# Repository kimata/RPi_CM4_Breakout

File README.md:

# RPi_CM4_Breakout

## 概要

Raspberry Pi Compute Module 4 から，通常の Raspberry Pi にあるピンヘッダを取り出す基板です．
サイズと穴位置は秋月のユニバーサル基板Ｃタイプに合わせてあります．

おまけで，I2C 用のピンヘッダ用のランドも設けています．

## 外観

## 回路図

## 基板の発注について

Raspberry Pi Compute Module 4 との接続に使う 100 ピンコネクタは手はんだが難しいので，この部分だけ基板メーカで実装してもらうのがおすすめです．

Elecrow にオーダーする際のシートを misc/Elecrow-PCBA-Quotation.xlsx においておきましたので参考にしてください．このファイルとガーバーデータを送れば製造できます．

料金は，私が製造したときは，送料込みで $168 でした．

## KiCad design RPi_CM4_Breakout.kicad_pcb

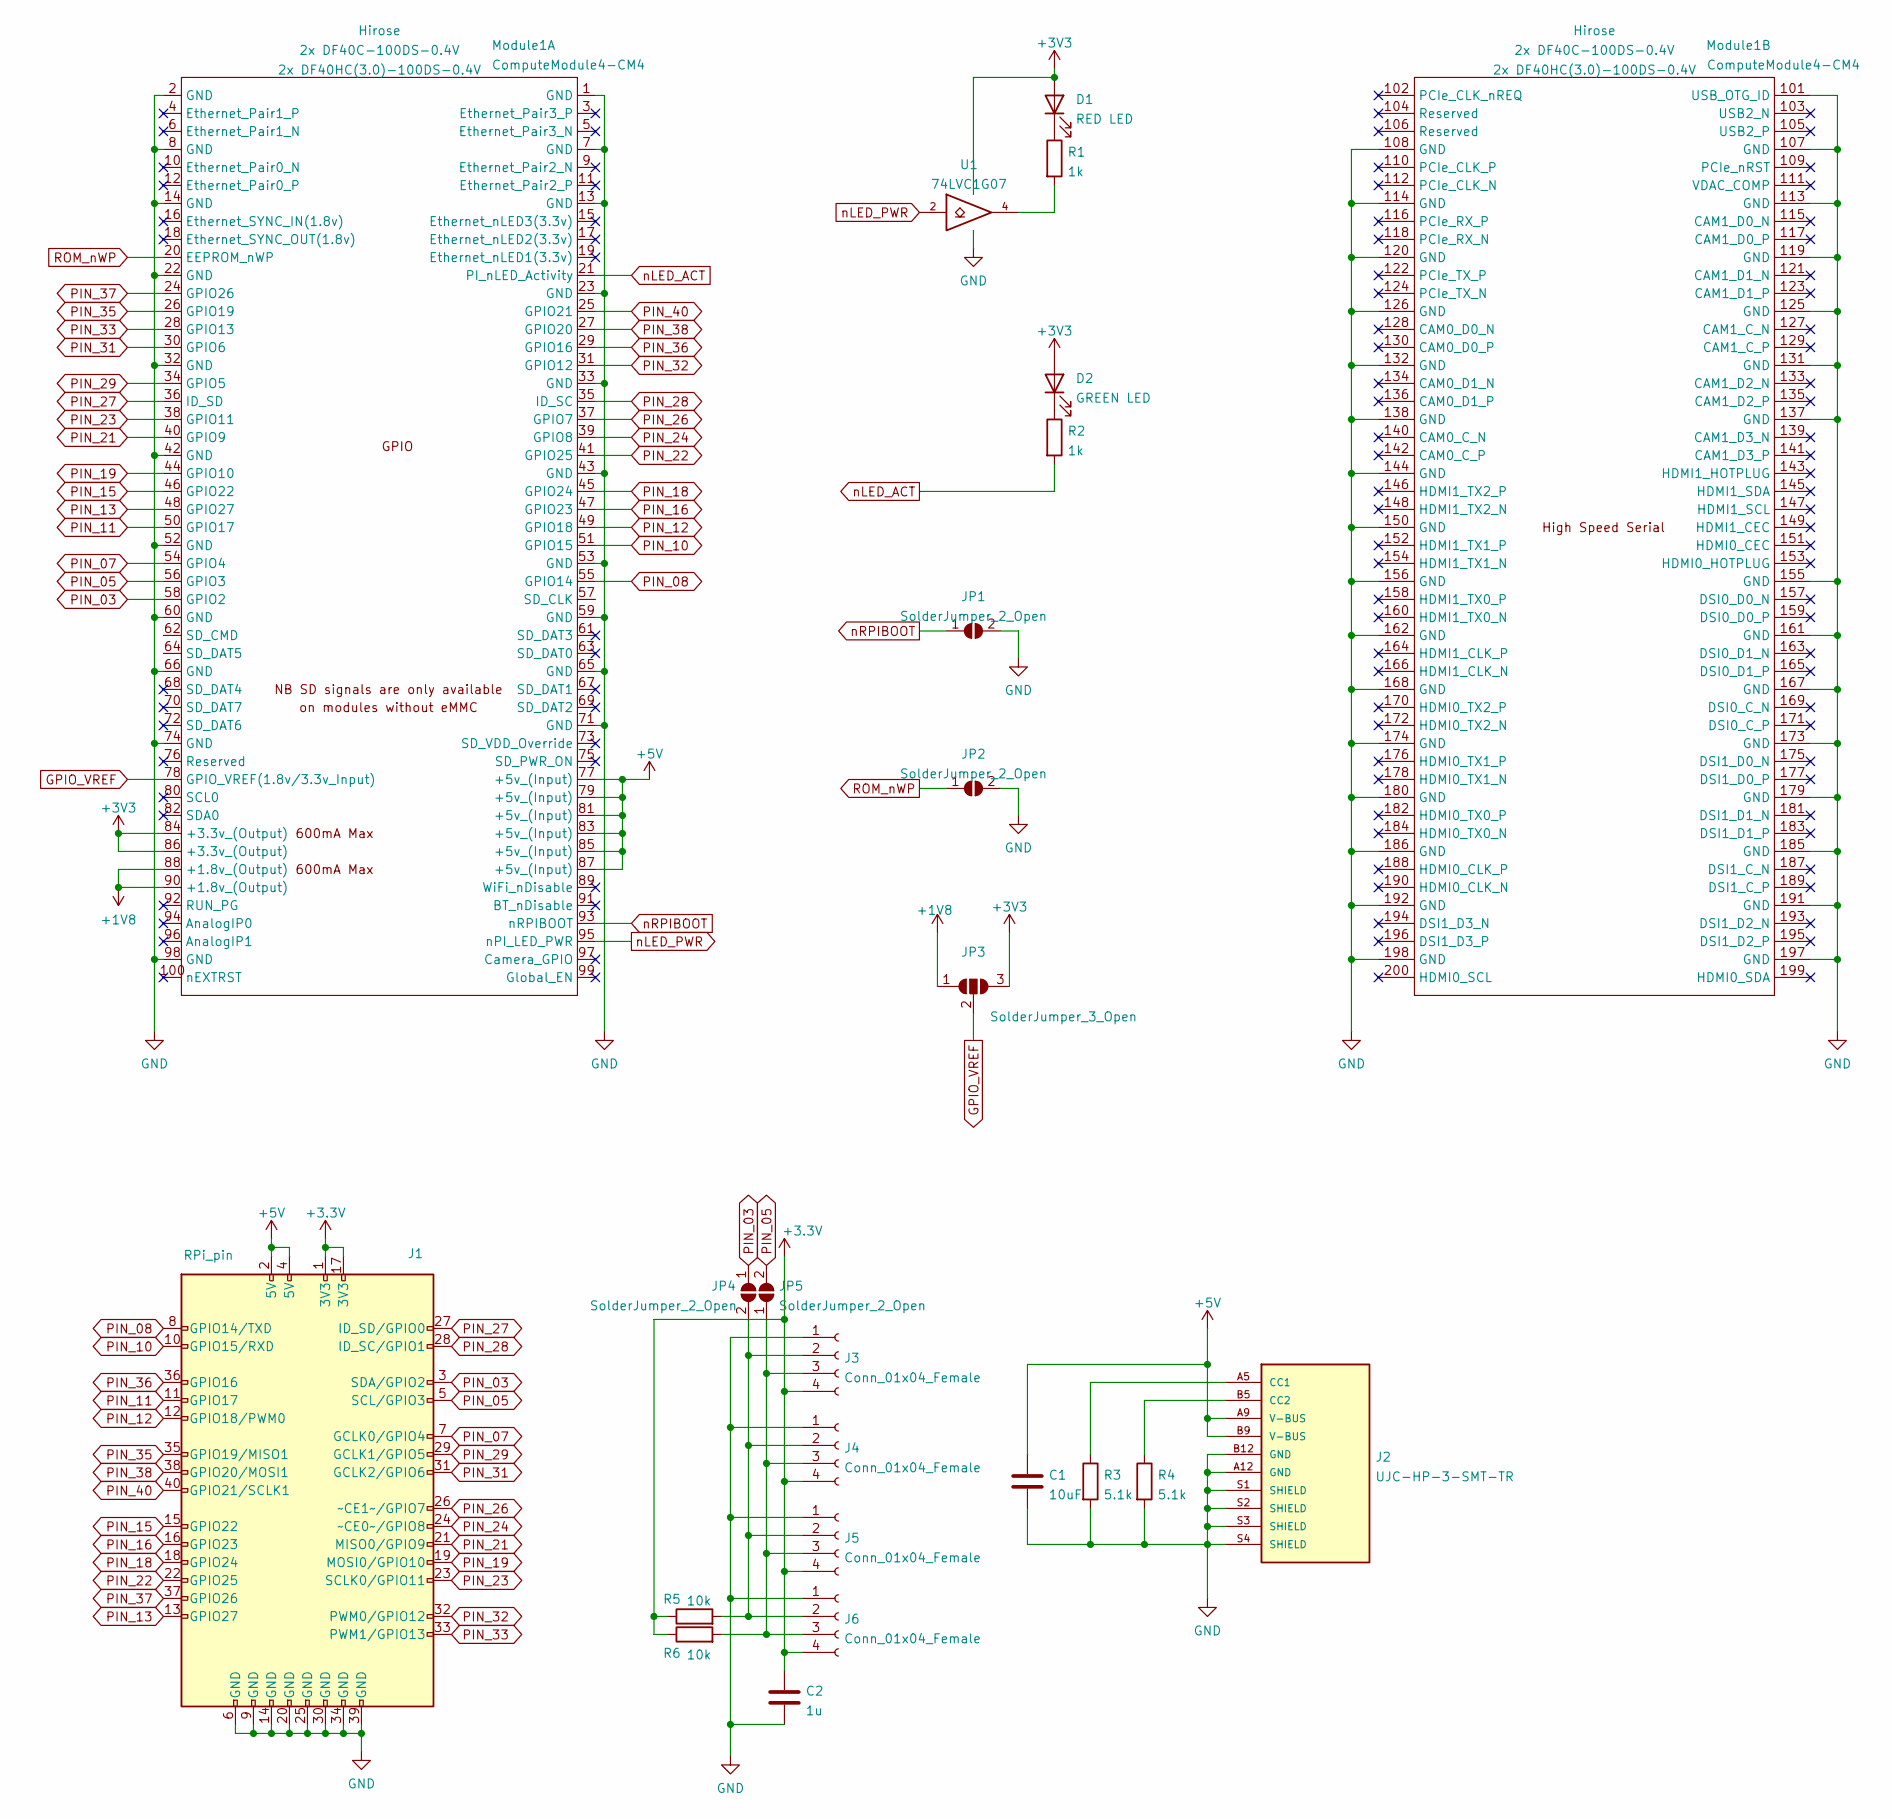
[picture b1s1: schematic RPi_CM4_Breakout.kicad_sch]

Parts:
C1: 10uF; C_1206_3216Metric_Pad1.33x1.80mm_HandSolder
C2: 1u; C_0805_2012Metric_Pad1.18x1.45mm_HandSolder
D1: RED LED; LED_0805_2012Metric_Pad1.15x1.40mm_HandSolder
D2: GREEN LED; LED_0805_2012Metric_Pad1.15x1.40mm_HandSolder
J1: RPi_pin; PinHeader_2x20_P2.54mm_Vertical
J2: UJC-HP-3-SMT-TR; CUI_UJC-HP-3-SMT-TR
J3, J4, J5, J6: Conn_01x04_Female; PinHeader_1x04_P2.54mm_Vertical
JP1, JP2, JP4, JP5: SolderJumper_2_Open; SolderJumper-2_P1.3mm_Open_RoundedPad1.0x1.5mm
JP3: SolderJumper_3_Open; SolderJumper-3_P1.3mm_Open_RoundedPad1.0x1.5mm
Module1: ComputeModule4-CM4; Raspberry-Pi-4-Compute-Module; MPN 2x DF40C-100DS-0.4V; Digi-Key_PN 2x H11615CT-ND
R1, R2: 1k; R_0805_2012Metric_Pad1.20x1.40mm_HandSolder
R3, R4: 5.1k; R_0805_2012Metric_Pad1.20x1.40mm_HandSolder
R5, R6: 10k; R_0805_2012Metric_Pad1.20x1.40mm_HandSolder
U1: 74LVC1G07; SOT-753

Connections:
+1V8: JP3.1 (A), Module1.88 (+1.8v_(Output)), Module1.90 (+1.8v_(Output))
+5V: C1.1, J1.2 (5V), J1.4 (5V), J2.A9 (V-BUS), J2.B9 (V-BUS), Module1.77 (+5v_(Input)), Module1.79 (+5v_(Input)), Module1.81 (+5v_(Input)), Module1.83 (+5v_(Input)), Module1.85 (+5v_(Input)), Module1.87 (+5v_(Input))
GND: C1.2, C2.2, J1.6 (GND), J1.9 (GND), J1.14 (GND), J1.20 (GND), J1.25 (GND), J1.30 (GND), J1.34 (GND), J1.39 (GND), J2.A12 (GND), J2.B12 (GND), J2.S1 (SHIELD), J2.S2 (SHIELD), J2.S3 (SHIELD), J2.S4 (SHIELD), J3.1, J4.1, J5.1, J6.1, JP1.2 (B), JP2.2 (B), Module1.1 (GND), Module1.2 (GND), Module1.7 (GND), Module1.8 (GND), Module1.13 (GND), Module1.14 (GND), Module1.22 (GND), Module1.23 (GND), Module1.32 (GND), Module1.33 (GND), Module1.42 (GND), Module1.43 (GND), Module1.52 (GND), Module1.53 (GND), Module1.59 (GND), Module1.60 (GND), Module1.65 (GND), Module1.66 (GND), Module1.71 (GND), Module1.74 (GND), Module1.98 (GND), Module1.101 (USB_OTG_ID), Module1.107 (GND), Module1.108 (GND), Module1.113 (GND), Module1.114 (GND), Module1.119 (GND), Module1.120 (GND), Module1.125 (GND), Module1.126 (GND), Module1.131 (GND), Module1.132 (GND), Module1.137 (GND), Module1.138 (GND), Module1.144 (GND), Module1.150 (GND), Module1.155 (GND), Module1.156 (GND), Module1.161 (GND), Module1.162 (GND), Module1.167 (GND), Module1.168 (GND), Module1.173 (GND), Module1.174 (GND), Module1.179 (GND), Module1.180 (GND), Module1.185 (GND), Module1.186 (GND), Module1.191 (GND), Module1.192 (GND), Module1.197 (GND), Module1.198 (GND), R3.2, R4.2, U1.3 (GND)
GPIO_VREF: JP3.2 (C), Module1.78 (GPIO_VREF(1.8v/3.3v_Input))
unnamed: D1.1 (K), R1.1
unnamed: D2.1 (K), R2.1
unnamed: J2.A5 (CC1), R3.1
unnamed: J2.B5 (CC2), R4.1
unnamed: J3.2, J4.2, J5.2, J6.2, JP4.2 (B), R5.2
unnamed: J3.3, J4.3, J5.3, J6.3, JP5.1 (A), R6.2
unnamed: R1.2, U1.4
PIN_03: J1.3 (SDA/GPIO2), JP4.1 (A), Module1.58 (GPIO2)
PIN_05: J1.5 (SCL/GPIO3), JP5.2 (B), Module1.56 (GPIO3)
PIN_07: J1.7 (GCLK0/GPIO4), Module1.54 (GPIO4)
PIN_08: J1.8 (GPIO14/TXD), Module1.55 (GPIO14)
PIN_10: J1.10 (GPIO15/RXD), Module1.51 (GPIO15)
PIN_11: J1.11 (GPIO17), Module1.50 (GPIO17)
PIN_12: J1.12 (GPIO18/PWM0), Module1.49 (GPIO18)
PIN_13: J1.13 (GPIO27), Module1.48 (GPIO27)
PIN_15: J1.15 (GPIO22), Module1.46 (GPIO22)
PIN_16: J1.16 (GPIO23), Module1.47 (GPIO23)
PIN_18: J1.18 (GPIO24), Module1.45 (GPIO24)
PIN_19: J1.19 (MOSI0/GPIO10), Module1.44 (GPIO10)
PIN_21: J1.21 (MISO0/GPIO9), Module1.40 (GPIO9)
PIN_22: J1.22 (GPIO25), Module1.41 (GPIO25)
PIN_23: J1.23 (SCLK0/GPIO11), Module1.38 (GPIO11)
PIN_24: J1.24 (~CE0~/GPIO8), Module1.39 (GPIO8)
PIN_26: J1.26 (~CE1~/GPIO7), Module1.37 (GPIO7)
PIN_27: J1.27 (ID_SD/GPIO0), Module1.36 (ID_SD)
PIN_28: J1.28 (ID_SC/GPIO1), Module1.35 (ID_SC)
PIN_29: J1.29 (GCLK1/GPIO5), Module1.34 (GPIO5)
PIN_31: J1.31 (GCLK2/GPIO6), Module1.30 (GPIO6)
PIN_32: J1.32 (PWM0/GPIO12), Module1.31 (GPIO12)
PIN_33: J1.33 (PWM1/GPIO13), Module1.28 (GPIO13)
PIN_35: J1.35 (GPIO19/MISO1), Module1.26 (GPIO19)
PIN_36: J1.36 (GPIO16), Module1.29 (GPIO16)
PIN_37: J1.37 (GPIO26), Module1.24 (GPIO26)
PIN_38: J1.38 (GPIO20/MOSI1), Module1.27 (GPIO20)
PIN_40: J1.40 (GPIO21/SCLK1), Module1.25 (GPIO21)
ROM_nWP: JP2.1 (A), Module1.20 (EEPROM_nWP)
nLED_ACT: Module1.21 (PI_nLED_Activity), R2.2
nLED_PWR: Module1.95 (nPI_LED_PWR), U1.2
nRPIBOOT: JP1.1 (A), Module1.93 (nRPIBOOT)

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
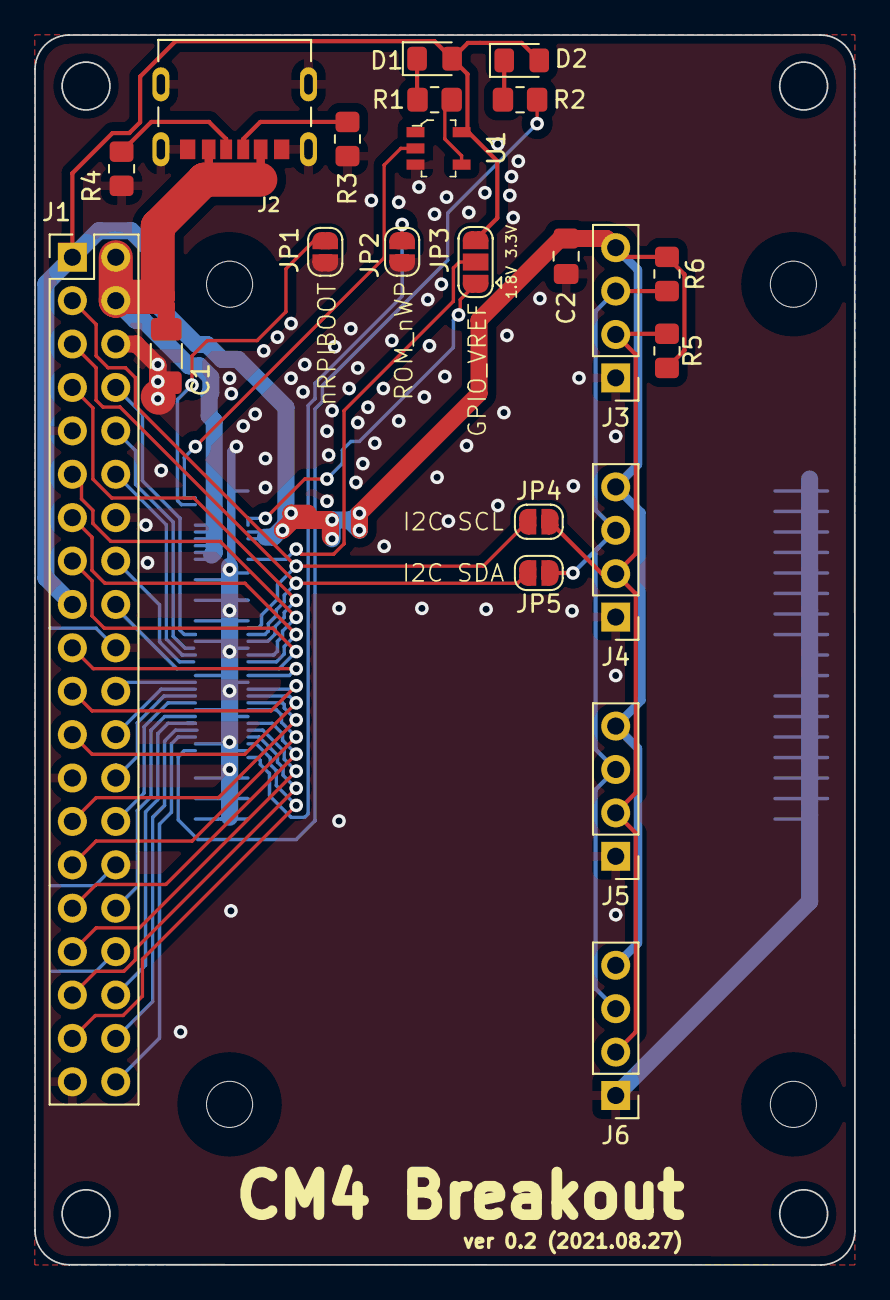
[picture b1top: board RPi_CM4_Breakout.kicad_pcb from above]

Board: 2 copper layers, 48.0 x 72.0 mm, 23 parts (1 on the bottom side), 44 nets.

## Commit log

2021-08-17 feat: とりあえず完成
2021-08-17 fix: 名前を変更
2021-10-08 doc: ドキュメントを追加
2021-10-08 fix: 調整
2021-10-08 fix: ファイル名の誤記を修正
2021-10-08 doc: 基板サイズについて追記
2021-10-10 fix: LED ドライバのパッケージを SOT753 に変更
